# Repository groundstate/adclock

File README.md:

Installation
------------

Setting up a BeagleBone Black
-----------------------------

Configuration file
------------------

`adclock` uses a configuration file `adclock.xml`. The comments in the sample file should be enough to get you going.
The search path for this is `./:~/adclock:~/.adclock:/usr/local/etc:/etc`
All other paths are explicit.

Known bugs/quirks
-----------------

Website
-------

There's a bit more information and screenshots at [ninepointtwoghz.org](http://ninepointtwoghz.org/analog-digital-clock.php)

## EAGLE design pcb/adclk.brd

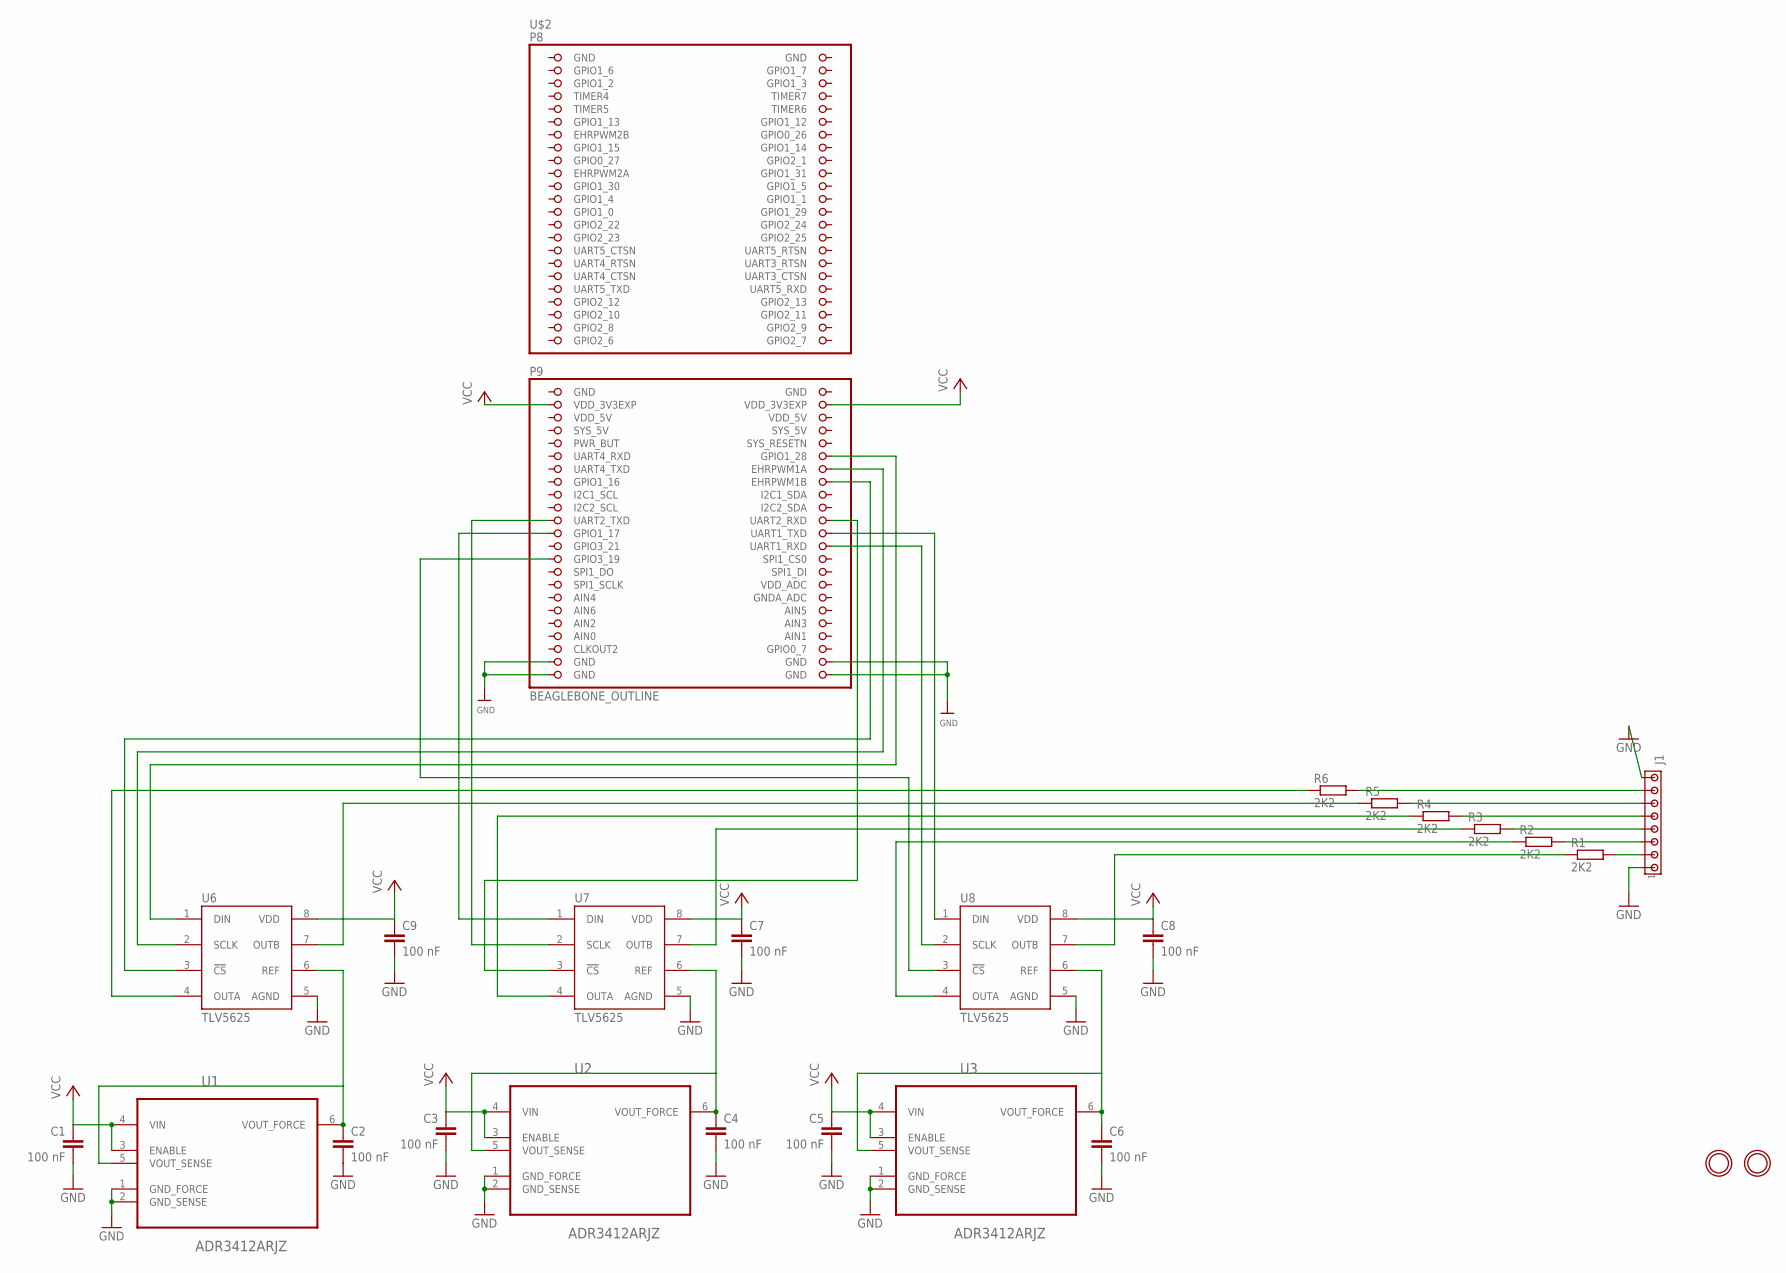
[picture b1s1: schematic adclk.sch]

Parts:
C1, C2, C3, C4, C5, C6, C7, C8, C9: 100 nF; C1808
J1: MTA08-100; 10X08MTA
R1, R2, R3, R4, R5, R6: 2K2; R0805
U1, U2, U3: ADR3412ARJZ; SOT95P280X145-6N
U6, U7, U8: TLV5625; SO8
U$2: BEAGLEBONE_OUTLINE; BEAGLEBONE_SHIELD
U$22, U$23: MOUNTINGHOLE3.0THIN; MOUNTINGHOLE_3.0_PLATEDTHIN

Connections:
AIN0: U$2.85 (AIN0)
AIN3: U$2.84 (AIN3)
GND: C1.2, C2.2, C3.2, C4.2, C5.2, C6.2, C7.2, C8.2, C9.2, J1.1, J1.8, U1.1 (GND_FORCE), U1.2 (GND_SENSE), U2.1 (GND_FORCE), U2.2 (GND_SENSE), U3.1 (GND_FORCE), U3.2 (GND_SENSE), U6.5 (AGND), U7.5 (AGND), U8.5 (AGND), U$2.1 (GND), U$2.2 (GND), U$2.47 (GND), U$2.48 (GND), U$2.89 (GND), U$2.90 (GND), U$2.91 (GND), U$2.92 (GND)
GPIO1_6: U$2.3 (GPIO1_6)
GPIO1_7: U$2.4 (GPIO1_7)
GPIO2_6: U$2.45 (GPIO2_6)
GPIO2_7: U$2.46 (GPIO2_7)
GPIO2_8: U$2.43 (GPIO2_8)
GPIO2_9: U$2.44 (GPIO2_9)
GPIO2_11: U$2.42 (GPIO2_11)
unnamed: J1.7, R6.2
unnamed: J1.6, R5.2
unnamed: J1.5, R4.2
unnamed: J1.4, R3.2
unnamed: J1.3, R2.2
unnamed: J1.2, R1.2
unnamed: C2.1, U1.5 (VOUT_SENSE), U1.6 (VOUT_FORCE), U6.6 (REF)
unnamed: R1.1, U8.7 (OUTB)
unnamed: C4.1, U2.5 (VOUT_SENSE), U2.6 (VOUT_FORCE), U7.6 (REF)
unnamed: R2.1, U8.4 (OUTA)
unnamed: C6.1, U3.5 (VOUT_SENSE), U3.6 (VOUT_FORCE), U8.6 (REF)
unnamed: R3.1, U7.7 (OUTB)
unnamed: R4.1, U7.4 (OUTA)
unnamed: R5.1, U6.7 (OUTB)
unnamed: R6.1, U6.4 (OUTA)
unnamed: U6.1 (DIN), U$2.58 (GPIO1_28)
unnamed: U6.2 (SCLK), U$2.60 (EHRPWM1A)
unnamed: U6.3 (!CS!), U$2.62 (EHRPWM1B)
unnamed: U8.1 (DIN), U$2.70 (UART1_TXD)
unnamed: U8.2 (SCLK), U$2.72 (UART1_RXD)
unnamed: U8.3 (!CS!), U$2.73 (GPIO3_19)
unnamed: U7.1 (DIN), U$2.69 (GPIO1_17)
unnamed: U7.3 (!CS!), U$2.68 (UART2_RXD)
unnamed: U7.2 (SCLK), U$2.67 (UART2_TXD)
VCC: C1.1, C3.1, C5.1, C7.1, C8.1, C9.1, U1.3 (ENABLE), U1.4 (VIN), U2.3 (ENABLE), U2.4 (VIN), U3.3 (ENABLE), U3.4 (VIN), U6.8 (VDD), U7.8 (VDD), U8.8 (VDD), U$2.49 (VDD_3V3EXP), U$2.50 (VDD_3V3EXP)
VDD_5V: U$2.51 (VDD_5V), U$2.52 (VDD_5V)

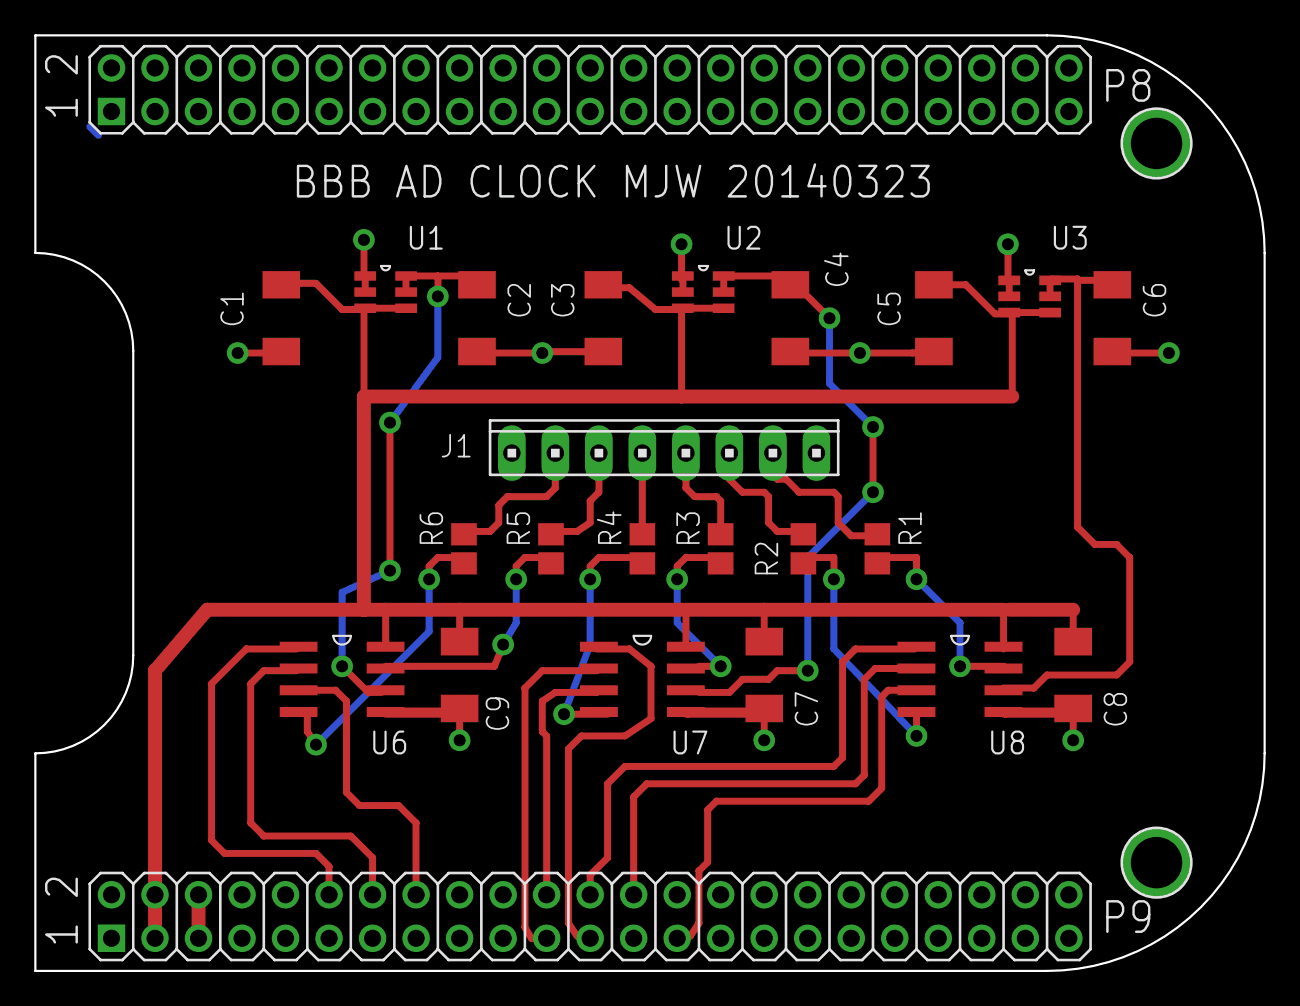
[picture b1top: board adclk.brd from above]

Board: 2 copper layers, 71.8 x 54.6 mm, 25 parts (0 on the bottom side), 27 nets.

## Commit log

2016-10-16 Added overlay. Note that an extra pin is used because of a dead pin on my BB.
2016-10-16 Many improvements.
2016-10-17 Last bits ? Alomost done.
2016-10-19 Added Eagle PCB files (since they are now verified to work!)
2017-02-05 Minor oopsies. Config file was broken. Ramp test had units/tens swapped.
2017-02-06 Better install. startup as systemd service. Bug fix - HOME not defined when running as a system service.
